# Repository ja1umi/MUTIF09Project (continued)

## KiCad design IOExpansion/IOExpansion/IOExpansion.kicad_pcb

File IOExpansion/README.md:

# MUTIF09 I/O Expansion Board (MUTIF09-IOEXP)

**Revision 3, works as expected (May 21, 2019)**

MUTIF09 I/O Expansion Board is designed to add I2C (5V and 3.3V), SPI (3.3V) and GPIO (data pins are 5V tolerant but 3.3V is preferable) connectivity and functionality via TTL serial connection. Basically, this board is intended for use together with the MUTIF09 6809 SBC but theoretically it can work with other single board computer with minimal modification.

MUTIF09 6809SBC sees this board as an additional asynchronous communication interface adapter (ACIA) and this board works as an interface between ACIA and the I2C- & SPI-bus. This allows the 6809 to communicate with other I2C- or SPI-bus deveices such as temperature sensor, Realtime clock, EEPROM, ADC, SRAM and so on through ACIA.

## Block Diagram

(You may need to install an extension, like [*mermaid-for-github-chrome-extension*][1] (for Google Chrome) to see this diagram correctly)

[1]:https://github.com/set0gut1/mermaid-for-github-chrome-extention

```mermaid
graph TD
  id0>MUTIF6809 SBC] --- 16550
  16550 --- id1[Level Shifter]
  id1 --- SC18IM700
  SC18IM700---|MST0|PCA9541
  PCA9541---|Slave|id2[I2C-Level Shifter]
  id2 --- id3[5V I2C Slave port]
  PCA9541---|Slave|id4[3.3V I2C Slave port]
  PCA9541---|Slave|id5["on board RTC (DS3231)"]
  id6>External I2C Master] --- ADuM1250
  ADuM1250---|MST1|PCA9541
  SC18IM700 --- SCIS602B
  SC18IS602B --- id7[SPI slave port]
  SC18IM700 --- id8["GPIO port (8 bits)"]
```

|Feature|Status|Implemented by using|
|-------|------|-------|
|Additional UART w/ FIFO|works|16550|
|UART-I2C (3.3 V, 5 V) bridge|works|SC18IM700, BSS138|
|UART-SPI (3.3 V) bridge|works|SC18IM700, SC18IS602B|
|GPIO (8 bit, 3.3 V)|works|SC18IM700|
|I2C-bus master selection|works|PCA9541|
|On-board RTC|works|DS3231 w/ backup battery|
||||

## Memory Maps

|Address|Register|
|-------|--------|
|$B020|Receiver Buffer Reg. /Transmitter Holding Reg.|
|$B021|Interrupt Enable Reg./Interrupt Indent. Reg.|
|$B022|FIFO Control Reg.|
|$B023|Line Control Reg.|
|$B024|MODEM Control Reg.|
|$B025|Line Status Reg.|
|$B026|MODEM Status Reg.|
|$B027|Scratch Reg.|
|$B020|Divisor Latch (Lo byte) if MSB of Line Control Reg. is 1|
|$B021|Divisor Latch (Hi byte) if MSB of Line Control Reg. is 1|
|||

## Documentation

This board has many features and therefore, I think that it needs documentation and examples. In this regard, I wrote a booklet about this and it will be available on the 4th day (August 12) of Comic Market 96 (Ariake, Tokyo, Japan) at booth# 南ラ13b and at BOOTH ( https://m-nihombashi.booth.pm/ ) thereafter. For now, please refer to the corresponding datasheets.

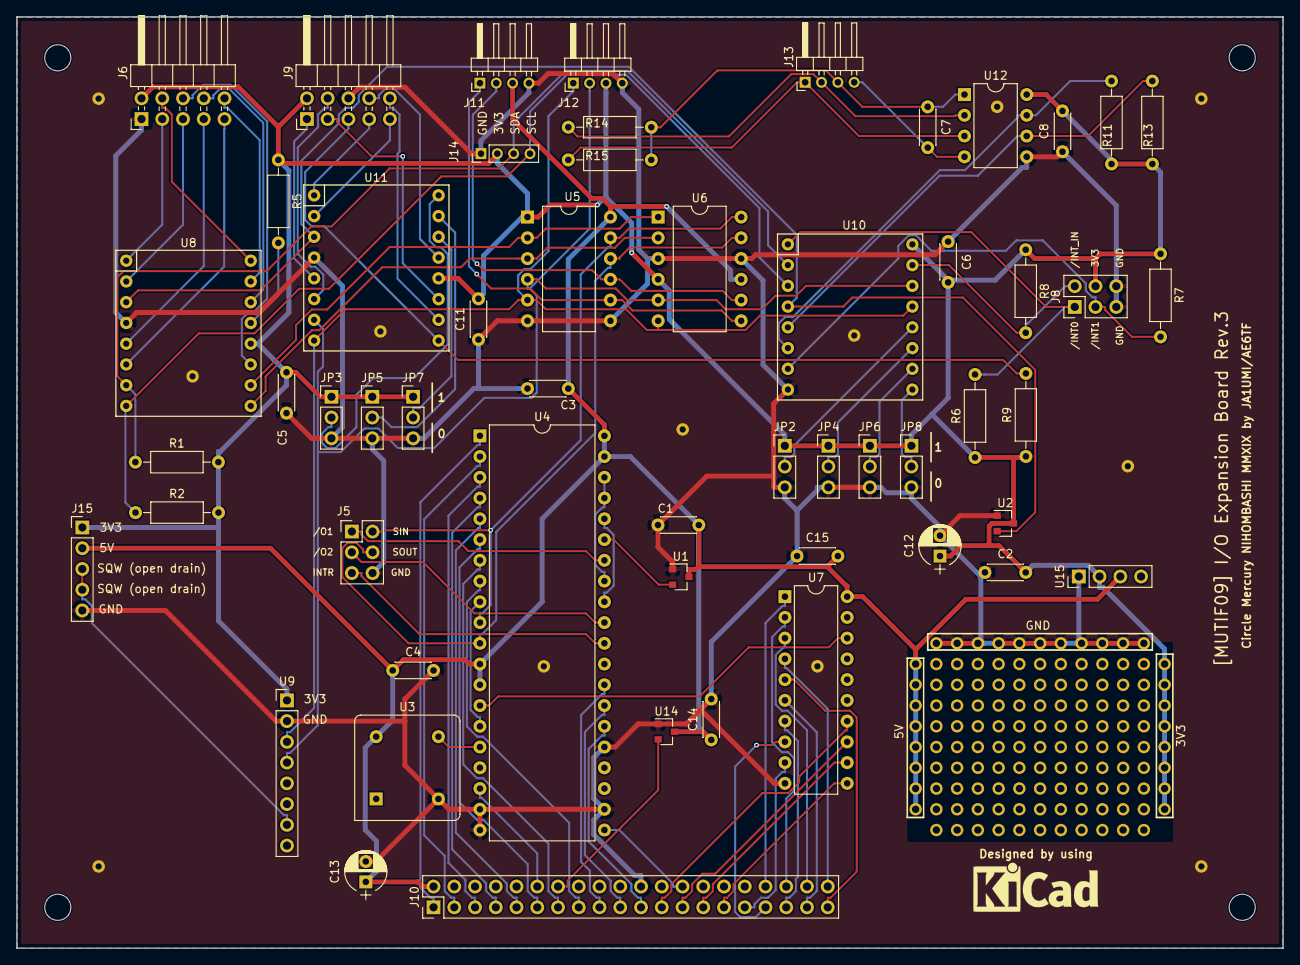
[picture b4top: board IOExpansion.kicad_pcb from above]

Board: 2 copper layers, 155.0 x 114.0 mm, 185 parts (0 on the bottom side), 84 nets.

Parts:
C1, C2, C3, C4, C5, C6, C7, C8, C11, C14, C15: 0.1u; C_Disc_D4.3mm_W1.9mm_P5.00mm
C12, C13: 10u; CP_Radial_D5.0mm_P2.50mm
J1, J2, J3, J4: Mount_Hole_3.2mm_M3; MountingHole_3.2mm_M3
J5: UART_5V; Pin_Header_Straight_2x03_Pitch2.54mm
J6: GPIO_3V3; Pin_Header_Angled_2x05_Pitch2.54mm
J8: I2C_INT; Pin_Header_Straight_2x03_Pitch2.54mm
J9: SPI_3V3; Pin_Header_Angled_2x05_Pitch2.54mm
J10: HEADER 2x20; Pin_Header_Straight_2x20_Pitch2.54mm
J11: I2C_5V; Pin_Header_Angled_1x04_Pitch2.00mm
J12: I2C_3V3; Pin_Header_Angled_1x04_Pitch2.00mm
J13: I2C_ALT_Master; Pin_Header_Angled_1x04_Pitch2.00mm
J14: I2C_Debug_3V3; Pin_Header_Straight_1x04_Pitch2.00mm
J15: SQW_OUT; Pin_Header_Straight_1x05_Pitch2.54mm
JP2: A3; Pin_Header_Straight_1x03_Pitch2.54mm
JP3, JP4: A2; Pin_Header_Straight_1x03_Pitch2.54mm
JP5, JP6: A1; Pin_Header_Straight_1x03_Pitch2.54mm
JP7, JP8: A0; Pin_Header_Straight_1x03_Pitch2.54mm
R1, R2, R11, R13: 10K; R_Axial_DIN0207_L6.3mm_D2.5mm_P10.16mm_Horizontal
R5: 1K; R_Axial_DIN0207_L6.3mm_D2.5mm_P10.16mm_Horizontal
R6, R7, R8, R9: 4.7K; R_Axial_DIN0207_L6.3mm_D2.5mm_P10.16mm_Horizontal
R14, R15: R; R_Axial_DIN0207_L6.3mm_D2.5mm_P10.16mm_Horizontal
REF00, REF01, REF02, REF03, REF04, REF05, REF06, REF07, REF08, REF09, REF10, REF11, REF12, REF13, REF14, REF15, REF16, REF17, REF18, REF19, REF20, REF21, REF22, REF23, REF24, REF25, REF26, REF27, REF28, REF29, REF30, REF31, REF32, REF33, REF34, REF35, REF36, REF37, REF38, REF39, REF40, REF41, REF42, REF43, REF44, REF45, REF46, REF47, REF48, REF49, REF50, REF51, REF52, REF53, REF54, REF55, REF56, REF57, REF58, REF59, REF60, REF61, REF62, REF63, REF64, REF65, REF66, REF67, REF68, REF69, REF70, REF71, REF72, REF73, REF74, REF75, REF76, REF77, REF78, REF79, REF80, REF81, REF82, REF83, REF84, REF85, REF86, REF87, REF88, REF89, REF90, REF91, REF92, REF93, REF94, REF95, REF96, REF97, REF98, REF99, REF100, REF101, REF102, REF103, REF104, REF105, REF106, REF107, REF108, REF109, REF110, REF111, REF112, REF113, REF114, REF115, REF116, REF117, REF118, REF119, REF120, REF121, REF122, REF123, REF124, REF125: pad
U1: MCP810-450; SOT-23
U2: MCP809-315; SOT-23
U3: SG-8002DC; Oscillator_DIP-8
U4: PC16550D; DIP-40_W15.24mm
U5: 4ch_Level_Shifter_BSS138; DIP-12_W10.16mm
U6: 4ch_Level_Shifter_BSS138(AKI); DIP-12_W10.16mm
U7: GAL16V8; DIP-20_W7.62mm
U8: SC18IM700; DIP-16_W15.24mm
U9: DS3231_Breakout; Pin_Header_Straight_1x08_Pitch2.54mm
U10: PCA9641 (or PCA9541); DIP-16_W15.24mm
U11: SC18IS602B; DIP-16_W15.24mm
U12: ADuM1250; DIP-8_W7.62mm
U14: MCP809-450; SOT-23
U15: LM3671_Breakout; Pin_Header_Straight_1x04_Pitch2.54mm

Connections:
/+3V3: C2.2, C5.1, C6.2, C8.2, C11.2, C12.1, J6.2, J8.4, J9.2, J12.3, J14.2, J15.1, JP2.1, JP3.1, JP4.1, JP5.1, JP6.1, JP7.1, JP8.1, R1.2, R2.2, R5.1, R6.1, R7.1, R8.1, R9.1, R11.1, R13.1, REF118.1, REF119.1, REF120.1, REF121.1, REF122.1, REF123.1, REF124.1, REF125.1, U2.3, U5.1, U6.4, U8.12, U9.1, U10.16, U11.12, U12.8, U15.2
/+5V: C1.2, C3.1, C4.1, C13.1, C14.1, C15.2, J10.2, J11.3, J15.2, REF110.1, REF111.1, REF112.1, REF113.1, REF114.1, REF115.1, REF116.1, REF117.1, U1.3, U3.8, U4.12, U4.13, U4.39, U4.40, U5.12, U6.9, U7.20, U14.3, U15.3
//INT0: J8.1, R6.2, U10.1
//INT1: J8.3, R7.2, U10.7
//INT_IN: J8.2, R8.2, U10.15
//INT_SPI: J9.5, R9.2, U11.9
//O1: J5.1, U4.34
//O2: J5.3, U4.31
//RESET: U2.2, U8.3, U10.4, U11.3
//R_W: J10.26, U4.21
//SS0_GPIO0: J9.7, U11.1
//SS1_GPIO1: J9.9, U11.2
//SS2_GPIO2: J9.10, U11.10
//SS3_GPIO3: J9.8, U11.13
//SYS_RES: J10.14, U14.2
//UARTCE: U4.14, U7.18
/A0: J10.17, U4.28
/A1: J10.19, U4.27
/A2: J10.21, U4.26
/A3: J10.23, U7.14
/A4: J10.25, U7.13
/A5: J10.27, U7.12
/A6: J10.29, U7.11
/A7: J10.31, U7.9
/A8: J10.33, U7.8
/A9: J10.35, U7.7
/A10: J10.37, U7.6
/A11: J10.39, U7.5
/A12: J10.40, U7.4
/A13: J10.38, U7.3
/A14: J10.36, U7.2
/A15: J10.34, U7.1
/AB0: JP8.2, U10.9
/AB1: JP6.2, U10.10
/AB2: JP4.2, U10.11
/AB3: JP2.2, U10.12
/AS0: JP7.2, U11.14
/AS1: JP5.2, U11.15
/AS2: JP3.2, U11.16
/CLK: U3.5, U4.16
/D0: J10.1, U4.1
/D1: J10.3, U4.2
/D2: J10.5, U4.3
/D3: J10.7, U4.4
/D4: J10.9, U4.5
/D5: J10.11, U4.6
/D6: J10.13, U4.7
/D7: J10.15, U4.8
/GND: C1.1, C2.1, C3.2, C4.2, C5.2, C6.1, C8.1, C11.1, C12.2, C13.2, C14.2, C15.1, J5.6, J6.1, J8.5, J8.6, J9.6, J10.22, J11.4, J12.4, J14.1, J15.5, JP2.3, JP3.3, JP4.3, JP5.3, JP6.3, JP7.3, JP8.3, REF00.1, REF01.1, REF02.1, REF03.1, REF04.1, REF05.1, REF06.1, REF07.1, REF08.1, REF09.1, REF10.1, U1.1, U2.1, U3.4, U4.19, U4.20, U4.22, U4.25, U5.6, U5.7, U6.3, U6.10, U7.10, U8.4, U9.2, U10.8, U11.4, U12.5, U14.1, U15.1
/GPIO0: J6.3, U8.1
/GPIO1: J6.5, U8.2
/GPIO2: J6.7, U8.5
/GPIO3: J6.9, U8.6
/GPIO4: J6.10, U8.15
/GPIO5: J6.8, U8.14
/GPIO6: J6.6, U8.11
/GPIO7: J6.4, U8.16
/INTR: J5.5, U4.30
/MISO: J9.1, U11.5
/MOSI: J9.4, U11.6
/RST: U1.2, U4.35
/RX: U5.3, U6.2, U8.9
/R_/W: J10.12, U4.18
/SCL_MST0: J14.4, R2.1, U8.8, U10.3
/SCL_MST1: R13.2, U10.5, U12.6
/SCL_SLAVE: J12.1, U5.5, U6.6, U9.3, U10.13, U11.8
/SCL_SLAVE_5V: J11.1, U5.8, U6.7
/SDA_MST0: J14.3, R1.1, U8.7, U10.2
/SDA_MST1: R11.2, U10.6, U12.7
/SDA_SLAVE: J12.2, U5.4, U6.5, U9.4, U10.14, U11.7
/SDA_SLAVE_5V: J11.2, U5.9, U6.8
/SIN: J5.2, U4.10, U5.11, U6.12
/SOUT: J5.4, U4.11, U5.10, U6.11
/SPICLK: J9.3, U11.11
/TX: U5.2, U6.1, U8.10
unnamed: C7.1, J13.3, R14.2, R15.2, U12.1
unnamed: C7.2, J13.4, U12.4
unnamed: J13.1, R15.1, U12.3
unnamed: J13.2, R14.1, U12.2
unnamed: J15.3, J15.4, U9.7
unnamed: R5.2, U8.13
unnamed: U4.9, U4.15
unnamed: U4.32, U4.36
unnamed: U4.33, U4.37, U4.38

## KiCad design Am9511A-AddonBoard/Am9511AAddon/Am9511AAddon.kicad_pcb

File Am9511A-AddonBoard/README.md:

# Am9511A Add-on Board for MUTIF09 6809 SBC

## TL;DR

This daughterboard is designed to add the functionlity of AMD Am9511A Arithmetic co-processor to MUTIF09 6809 SBC.

## Making short story long

I have been wanting to experience how arithmetic co-processor programming looks like. For this purpose, Am9511A sounds good because the dataseet says *"...The Am9511A APU is designed with a general purpose 8-bit data bus and interface control so that it can be conveniently used with any general 8-bit processor."* (ok. I should have realized the old saying: there is no rule without some exceptions). So, at first, I designed to connect Am9511A directly to the data bus of 6809 microprocessor with no success. I could not neither read nor write data from/to Am9511A as I expected. Good grief!

After Googling, finally, I found a document titled *"AMD Peripheral Processor Interface Guide Technical Manual"* which explains how to interface Am9511A with 6809, together with schematic drawing. Great. That was what I needed but the promlems were that 1) additional circuitry is required and 2) hard-to-get AMD logic ICs (Am25LS2519 and Am2956) are deployed.

Am25LS2519 and Am2956 are quad register with two independently controlled 3-state outputs and octal latches with 3-state outputs, respectively. These ICs are **very difficuly to find nowadays**. This is especially true for Am25LS2519. Further investigation revealed that a guru succeeded in developing a Am25LS2519 replecement board in standard logic ICs [1]. As for Am2956, it has quite similar functionality with 74LS373 or 74LS573. Besides つのぜみ-san (@ossanmed) kindly referred me to the articles about interfacing Am9511A with various microprocessors such as 63C09, Z80 and 6502. On the basis of these pieces of information, I deceided to build the Am9511A Add-on board of my own.

From functinal point of view, this Add-on board is a faithful clone from the circuitry shown in Figure 9-1.1a MC6809 and Am9511A interface, in the interface guide technical manual (mentioned above) with substitution of standard logic ICs (74HCT574, 74HCT00, 74HCT04 and 74HCT573) for AMD logic ICs (Am25LS2519 and Am2956).

It has not been an easy road for me since I began to build the Add-on board. It took two months before I noticed that connection between **6809 MRDY** pin (pin 36) and **Am9511A /PAUSE** pin (pin 17) with appropriately weak (high resistance) pull-up resistor (10k ohm works) is key to success.

Reading data from the Am9511A does not work correctly without connection between both pins. Specifically, the lack of the connection causes the last command byte written to be misread as "first data byte" when attempting to read data from the Am9511A. "Empty read" is an easy but *ad hoc* solution. The problem is that the Am9511's internal stack pointer is disturbed by this extra read operation. So, the pointer location must be re-initialized by reset through Am9511A RESET pin. Obviously, this is not a smart solution.

Also, the connection with inappropriate strong pull-up resistor caused weird results; unexpected restarting and hang-up in my case. Exessive strong pull-up resistors (2.2k ohm) prevent transition from high to low and sometimes make the sytem unstable.

## Assembly: It's time to build the board

Schematic and gerber data are provided in this directory.

## Installation

Check the alignment of the pins in the APU Expansion Connector named "To Am9511 Add-on board" on the MUTIF09 6809 SBC and make sure it is correct. After that, insert the Add-on board into the APU Expansion Connector.

Jumper JP1 selects the clock source used for Am9511A CLK input. The clock source options are either the 6809 bus clock E (between pin 3 and pin 2 closed) or an on-board xtal oscillator (between pin 2 and pin 1 closed). Use jumper pin for this.

Jumper JP2 should be closed unless justified. See also schematic diagram.

Make the following connections:
 1) Pin 35 of 6809 (Q) to header pin 6 of the connector J1 (2x12) on the Add-on board. See also schematic diagram (for MUTIF09 6809 SBC PCB Rev.1 only).
 2) Header pin 3 (PC0) of GPIO Port C to pin 22 (RESET) of Am9511A (for MUTIF09 6809 SBC PCB Rev.1 only)
 3) Pin 36 of 6809 (MRDY) to header pin 5 of the connector J2 (1x6) on the Add-on board. See also schematic diagram (for MUTIF 6809 SBC PCB Rev.3).

## Usage

See the sample program under TestProgram directory.

## External Link(s)

[1] http://jrok.com/project/pengo_u74/pengo_ic74_u74.html

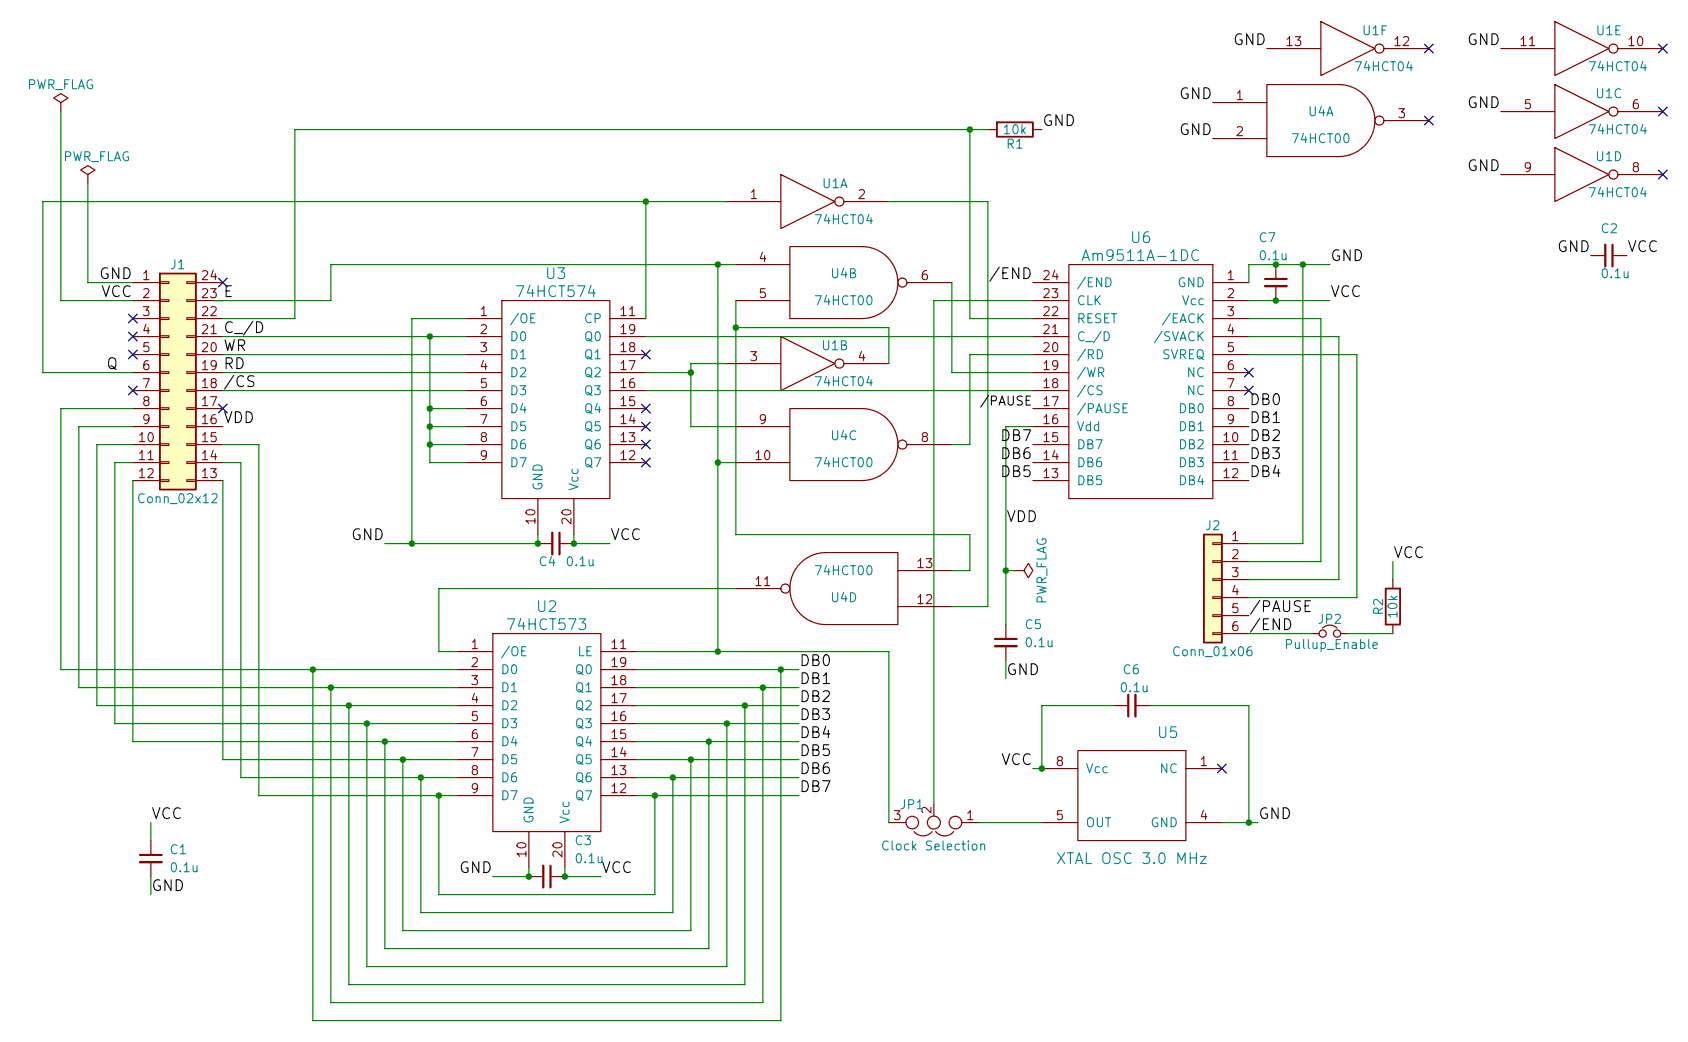
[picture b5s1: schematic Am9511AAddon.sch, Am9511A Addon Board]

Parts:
C1, C2, C3, C4, C5, C6, C7: 0.1u; C_Disc_D5.0mm_W2.5mm_P5.00mm
J1: Conn_02x12; DIP-24_W15.24mm
J2: Conn_01x06; Pin_Header_Straight_1x06_Pitch2.54mm
JP1: Clock Selection; Pin_Header_Straight_1x03_Pitch2.54mm
JP2: Pullup_Enable; Pin_Header_Straight_1x02_Pitch2.54mm
R1, R2: 10k; R_Axial_DIN0207_L6.3mm_D2.5mm_P10.16mm_Horizontal
U1: 74HCT04; DIP-14_W7.62mm
U2: 74HCT573; DIP-20_W7.62mm
U3: 74HCT574; DIP-20_W7.62mm
U4: 74HCT00; DIP-14_W7.62mm
U5: XTAL OSC 3.0 MHz; DIP-8_W7.62mm
U6: Am9511A-1DC; DIP-24_W15.24mm

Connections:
//CS: J1.18, U3.5 (D3)
//END: J2.6, JP2.1, U6.24 (/END)
//PAUSE: J2.5, U6.17 (/PAUSE)
/C_/D: J1.21, U3.2 (D0), U3.6 (D4), U3.7 (D5), U3.8 (D6), U3.9 (D7)
/DB0: J1.8, U2.2 (D0), U2.19 (Q0), U6.8 (DB0)
/DB1: J1.9, U2.3 (D1), U2.18 (Q1), U6.9 (DB1)
/DB2: J1.10, U2.4 (D2), U2.17 (Q2), U6.10 (DB2)
/DB3: J1.11, U2.5 (D3), U2.16 (Q3), U6.11 (DB3)
/DB4: J1.12, U2.6 (D4), U2.15 (Q4), U6.12 (DB4)
/DB5: J1.13, U2.7 (D5), U2.14 (Q5), U6.13 (DB5)
/DB6: J1.14, U2.8 (D6), U2.13 (Q6), U6.14 (DB6)
/DB7: J1.15, U2.9 (D7), U2.12 (Q7), U6.15 (DB7)
/E: J1.23, JP1.3, U2.11 (LE), U4.4, U4.10
/Q: J1.6, U1.1, U3.11 (CP)
/RD: J1.19, U3.4 (D2)
/VDD: C5.1, J1.16, U6.16 (Vdd)
/WR: J1.20, U3.3 (D1)
GND: C1.2, C2.2, C3.2, C4.2, C5.2, C6.2, C7.1, J1.1, J2.1, R1.1, U1.5, U1.7 (GND), U1.9, U1.11, U1.13, U2.10 (GND), U3.1 (/OE), U3.10 (GND), U4.1, U4.2, U4.7 (GND), U5.4 (GND), U6.1 (GND)
unnamed: J1.22, R1.2, U6.22 (RESET)
unnamed: J2.2, U6.3 (/EACK)
unnamed: J2.3, U6.4 (/SVACK)
unnamed: J2.4, U6.5 (SVREQ)
unnamed: JP1.1, U5.5 (OUT)
unnamed: JP1.2, U6.23 (CLK)
unnamed: JP2.2, R2.1
unnamed: U1.2, U4.12
unnamed: U1.3, U3.17 (Q2), U4.9
unnamed: U1.4, U4.5, U4.13
unnamed: U2.1 (/OE), U4.11
unnamed: U3.16 (Q3), U6.18 (/CS)
unnamed: U3.19 (Q0), U6.21 (C_/D)
unnamed: U4.6, U6.19 (/WR)
unnamed: U4.8, U6.20 (/RD)
VCC: C1.1, C2.1, C3.1, C4.1, C6.1, C7.2, J1.2, R2.2, U1.14 (VCC), U2.20 (Vcc), U3.20 (Vcc), U4.14 (VCC), U5.8 (Vcc), U6.2 (Vcc)

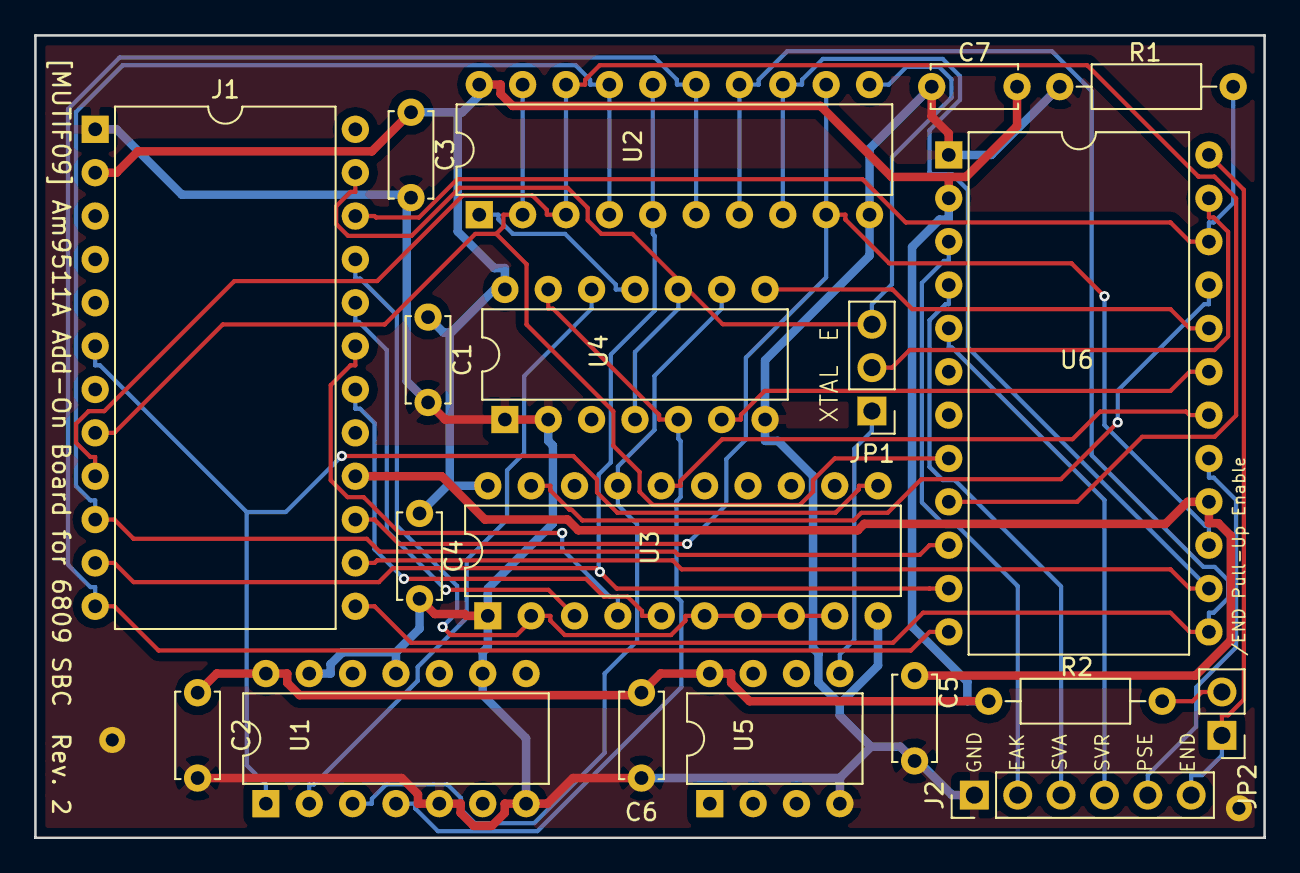
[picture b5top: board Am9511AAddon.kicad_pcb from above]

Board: 2 copper layers, 72.0 x 47.0 mm, 19 parts (0 on the bottom side), 34 nets.

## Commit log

2018-08-20 Update README.md and upload design materials (as of Augst 10, 2018; 1st day of Comic Maraket 94)
2018-08-20 Upload KiCad-related files
2018-08-20 Update README.md
    Fix typo
2018-08-21 Add test programs for 8255A
2018-09-05 Add test programs (for 8254 Programmable Interval Timer) and patch file to the monitor program
2018-09-13 Update design materials of 6809sbc and old files are moved to the archive directory (REV1)
2018-09-13 Update design files of 6809 SBC
2018-09-20 Update BOM
2018-10-09 Rename directory name add a test program for 8255A
2018-10-10 Update README.md (add FAQ item)
2018-10-10 Fix typo
2018-10-14 Update design materials of 6809sbc and old files are moved to the archive directory (REV2). Now My6809sbc directory contains REV3 design materials.
2018-10-14 Update schemetic of 6809SBC (now REV3)
2018-10-15 Update archive directories
2018-10-15 Add design materials of Am9511A Add-on board
2018-10-16 Add README file for Am9511A Add-on board
2018-10-18 Update BOM (6809Computer/My6809sbc/My6809sbc.csv) (Rev.3)
2018-10-18 Update README-Am9511AAddon.md (add acknowledgement)
2018-10-22 Remove compressed gerber file in GerberFiles_FusionPCB directory for better maintenance and for keeping consistency.
2018-10-22 Add design materials of I/O Expansion board
2018-10-26 Rename directory
2018-10-26 remove old directory
2018-10-26 Rename filename
2018-10-26 remove old file
2018-10-30 remove old directory (+1 squashed commits)
    Squashed commits:
    [e975237] Rename directory
2018-10-30 Rename directory name and add decimal from/to float conversion worksheet
2018-10-30 Rename directory and add conversion worksheet
2018-10-30 Old files are moved to the archive directory (REV1)
2018-10-30 Update design materials of Am9511A Add-on board (now, Rev.2)
2018-10-30 Remove obsolete/unnecessary files
2018-10-30 Update test program for Am9511A functionality
2018-10-30 Update README for Am9511A Add-on board
2018-10-30 Update README (test program)
2018-10-30 rename README file (test program)
2018-11-01 Update README.md (TtestProgram)
2018-11-15 Change directory structure from 6809Computer/My6809sbc to 6809Computer/My6809sbc/stable
2018-11-15 Rename directory name from My6809sbc to 6809sbc
2018-11-15 Add Python script(hex2data.py) and update README.md in Am9511A-AddonBoard/ProgrammingAid
2018-11-15 Change directory structure from Am9511A-AddonBoard/TestProgram/* to Am9511A-AddonBoard/TestProgram/square root/*
2018-11-15 Add modofied asciiart.bas and related files to Am9511A-AddonBoard/TestProgram/asciiart
2018-11-28 Add datasheets
2018-11-29 Update hex2data.py (add new option --noterm)
2018-11-29 Add MUTIF09 6809 SBC port of wnoy's (wnoy@yahoo.co.jp) MPB6809 Monitor (incl. hex file)
2018-11-29 Add new Test program (cumerr.bas) and related files to Am9511A-AddonBoard/TestProgram/addition10000times
2018-12-26 Add MUTIF09 6809 SBC port of MS Extended BASIC (incl. hex file)
2018-12-26 Add new Test program (c95example.bas) and related files to Am9511A-AddonBoard/TestProgram/c95example
2019-01-21 Update URL
2019-05-23 Update files for MUTIF09 I/O Expansion Board (Revision 3). Functionality tests were completed on May 21, 2019.
2019-08-07 Fix typo Add description on the booklet about IOExpansion board.
2019-08-07 Logic definition for GAL20V8B updated
2019-08-07 Add pointer to Leo (@Leo_yumeshichi)'s Blog.
2019-08-07 Bug fix in UPUTCH and and removal of unnecessary code in Init
2019-12-26 Add GPIOExpansion-, MemExpansion- and TMS9118VDP-Related files to the repository
2019-12-26 Rename file names
2019-12-26 Add processor check program
2019-12-26 Add design data as "testing" (Rev.4e)
2020-05-05 First commit for "PDP-8 on a chip" Harris HD6120 Evaluation-related files
2020-09-10 Update schematic and sketches (stable = hd6120-6_1.ino, testing = hd6120-8dio2_array_portreg_4)
2020-11-26 sample code (to calculate the 12th Finobacci number) extracted from the sketch (addCodes()) added
2020-11-26 Checking sheet (for Fibonacci number) added
2020-11-26 Sketch and schematic are updated. Sketch in "Testing" is now copied to "Stable"
2020-11-26 Update README.md
    Some minor corrections
2020-11-26 Update README.md
    Add COVID-19 notice
2020-12-02 Add some photos and movies in action
2020-12-04 Add Arduino Sketch/README.md
2020-12-04 Fix typo in Arduino Sketch/README.md
2020-12-09 Fix typo in Arduino Sketch/README.md
2020-12-22 Fix typos (README.MD, Arduino Sketch\README.md, and Schematic\README.md
2020-12-24 Fix typo in Schematic/README.md
